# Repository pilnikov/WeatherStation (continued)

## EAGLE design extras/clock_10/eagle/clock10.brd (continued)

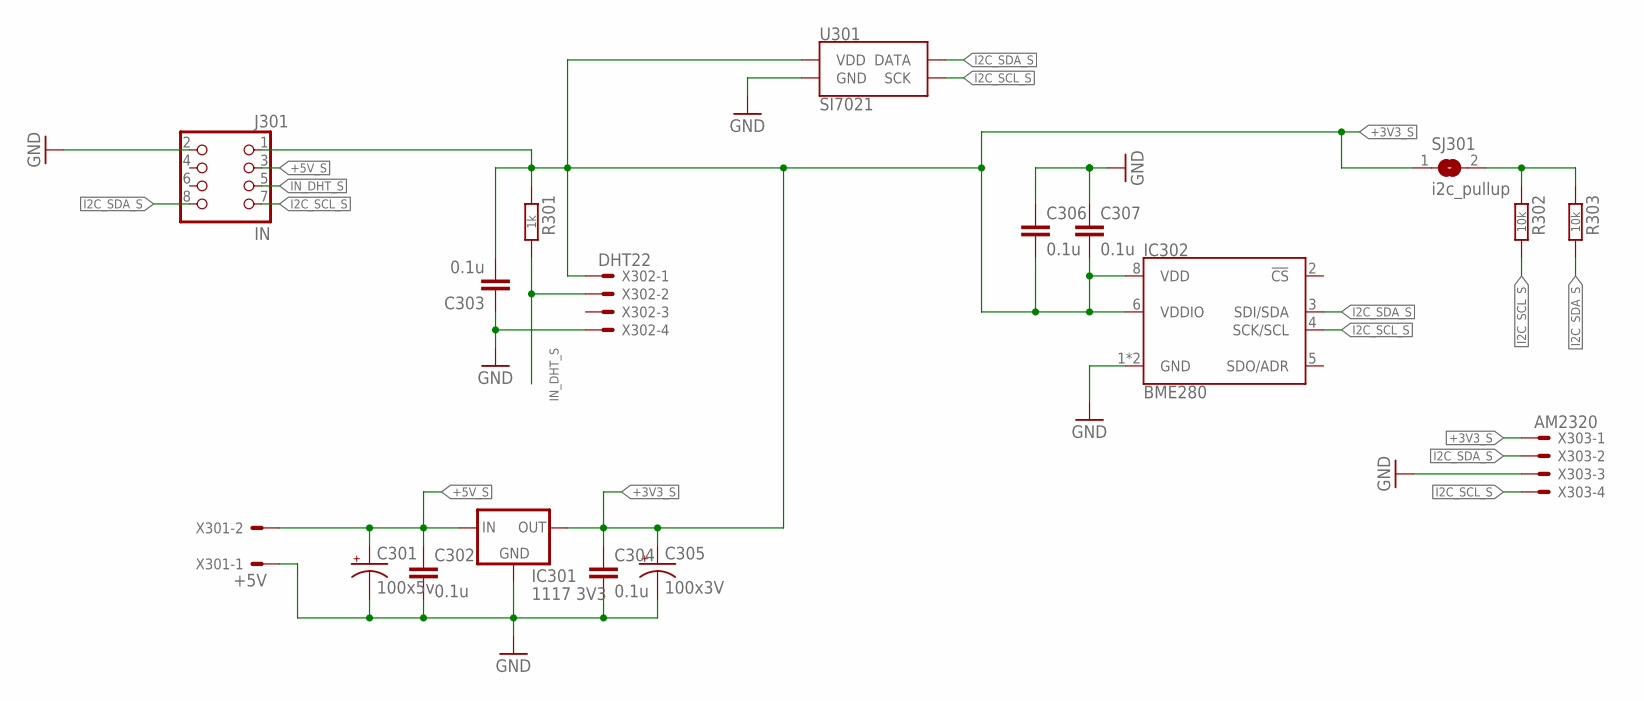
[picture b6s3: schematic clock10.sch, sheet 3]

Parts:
C301: 100x5v; CPOL-RADIAL-100UF-25V
C302, C303, C304, C306, C307: 0.1u; 0603-CAP
C305: 100x3V; CPOL-RADIAL-100UF-25V
IC301: 1117 3V3; SOT223
IC302: BME280; LGA-8-2.5X2.5
J301: IN; 2X04
R301: 1k; R0603
R302, R303: 10k; R0603
SJ301: i2c_pullup; MICROBUILDER_SOLDERJUMPER_ARROW_NOPASTE
U301: SI7021; DFN-6-3X3-SI7021
X301: +5V; 70543-02
X302: DHT22; 70543-04
X303: AM2320; 70543-04

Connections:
+3V3_S: C303.2, C304.1, C305.1 (+), C306.2, C307.2, IC301.2 (OUT), IC301.4 (OUT), IC302.6 (VDDIO), IC302.8 (VDD), J301.1, R301.1, SJ301.1, U301.VDD, X302.1, X303.1
+5V_S: C301.1 (+), C302.1, IC301.3 (IN), J301.3, X301.2
GND: C301.2 (-), C302.2, C303.1, C304.2, C305.2 (-), C306.1, C307.1, IC301.1 (GND), IC302.1 (GND), IC302.7 (GND), J301.2, U301.GND, X301.1, X302.4, X303.3; also elsewhere on the board
I2C_SCL_S: IC302.4 (SCK/SCL), J301.7, R302.2, U301.SCK, X303.4
I2C_SDA_S: IC302.3 (SDI/SDA), J301.8, R303.2, U301.DATA, X303.2
IN_DHT_S: J301.5, R301.2, X302.2
unnamed: R302.1, R303.1, SJ301.2

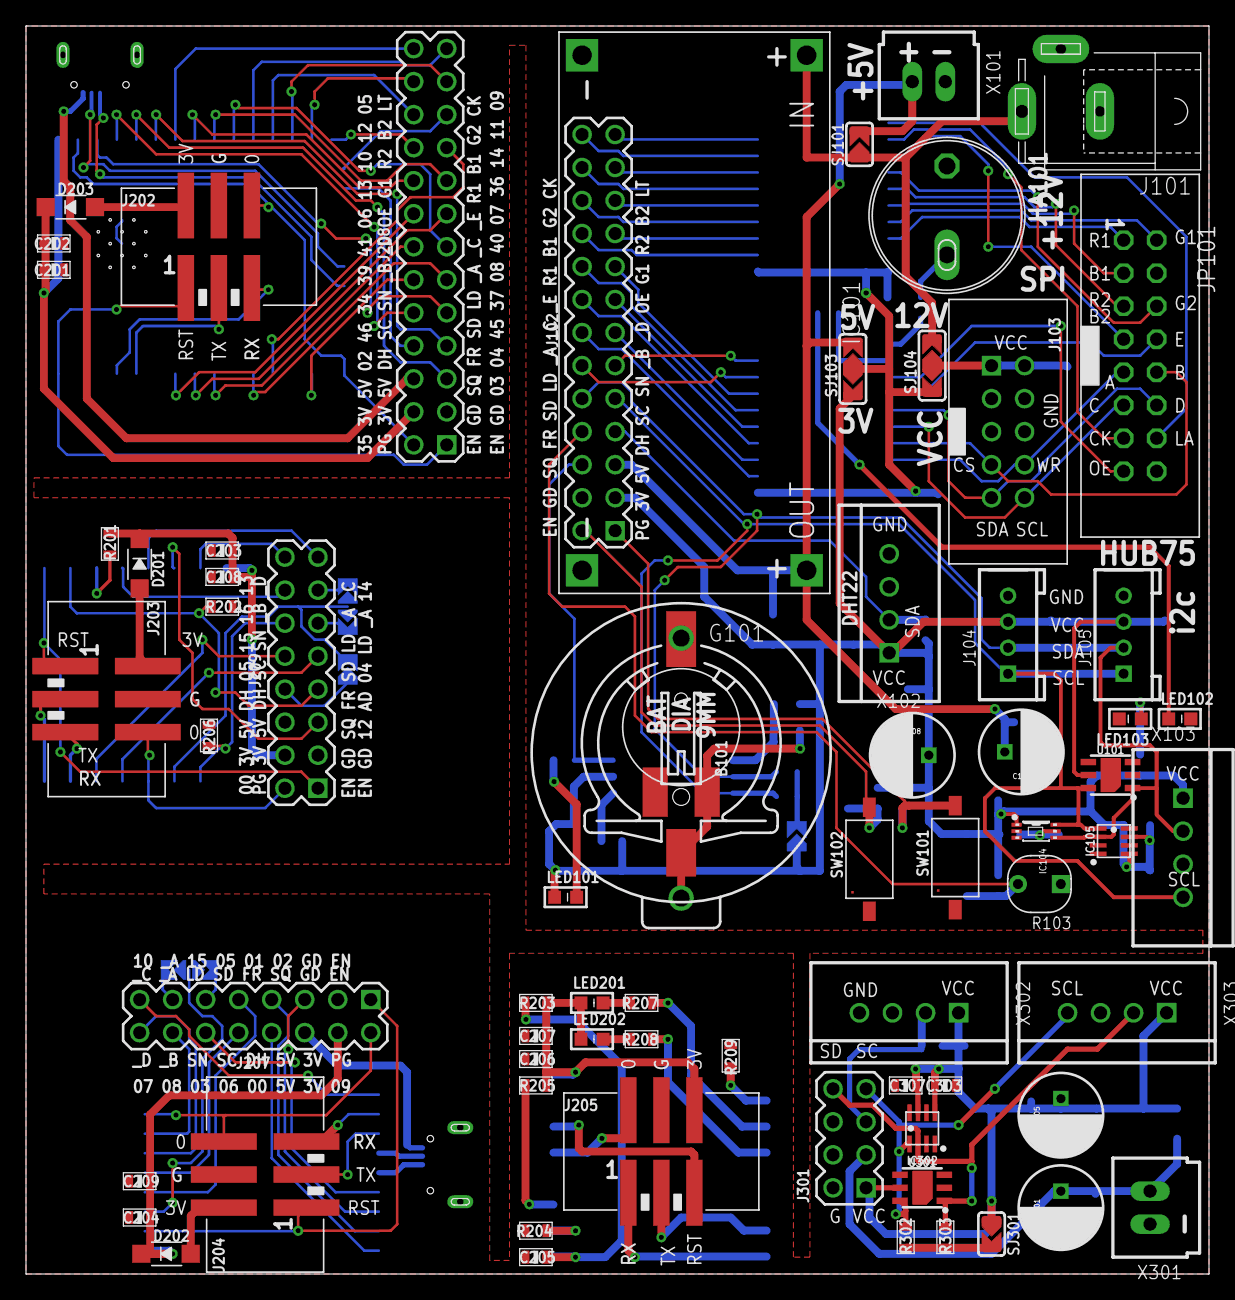
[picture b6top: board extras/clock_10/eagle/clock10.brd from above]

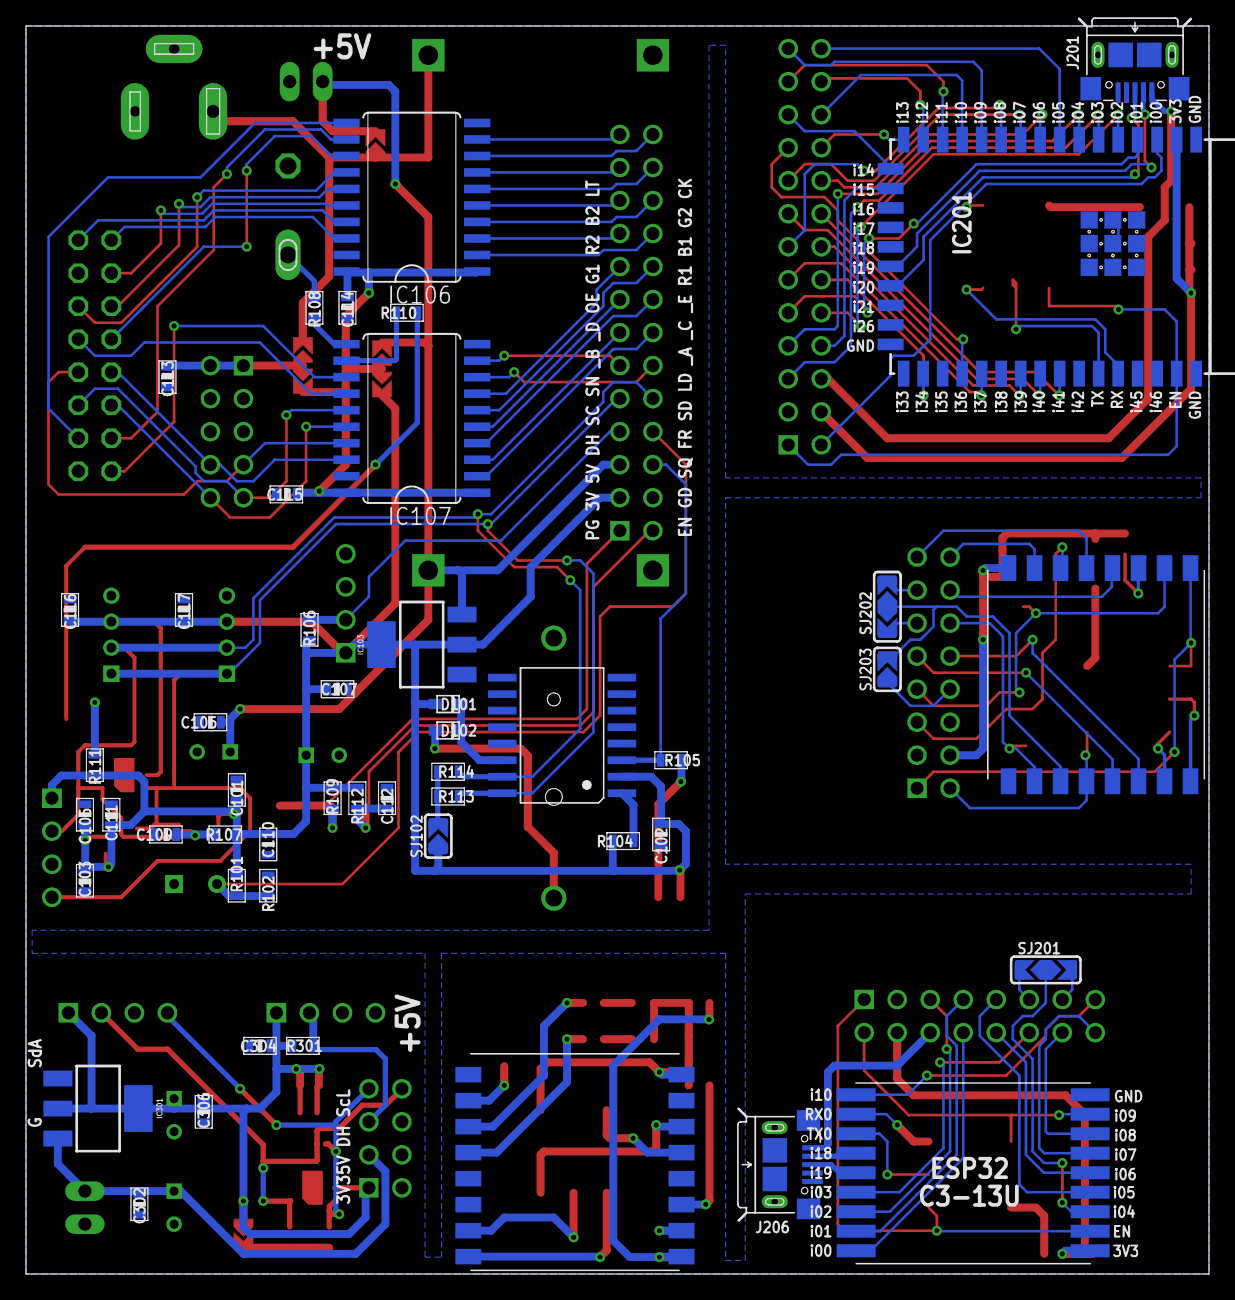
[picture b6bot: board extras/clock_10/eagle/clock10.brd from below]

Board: 2 copper layers, 91.0 x 96.0 mm, 120 parts (49 on the bottom side), 143 nets.

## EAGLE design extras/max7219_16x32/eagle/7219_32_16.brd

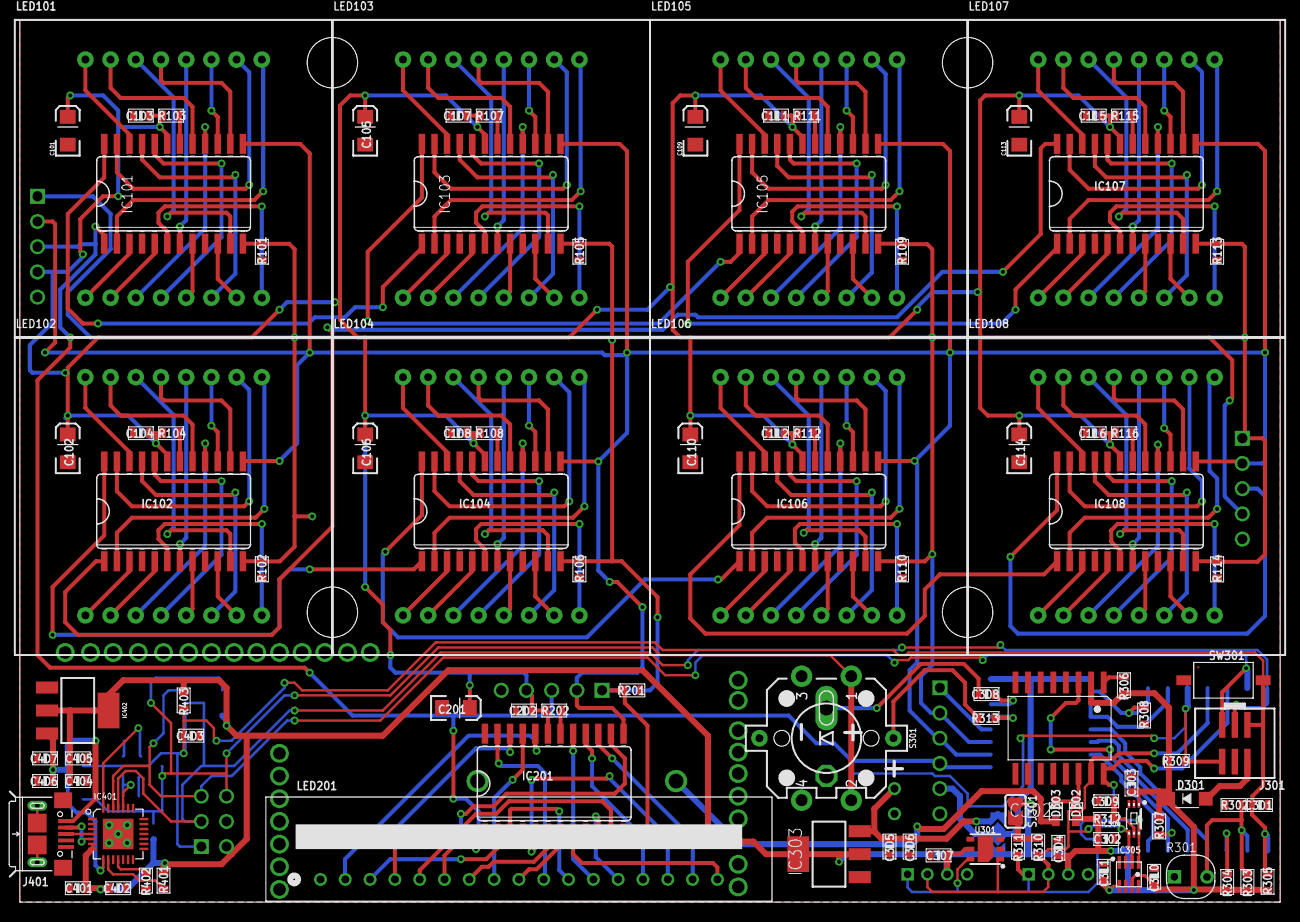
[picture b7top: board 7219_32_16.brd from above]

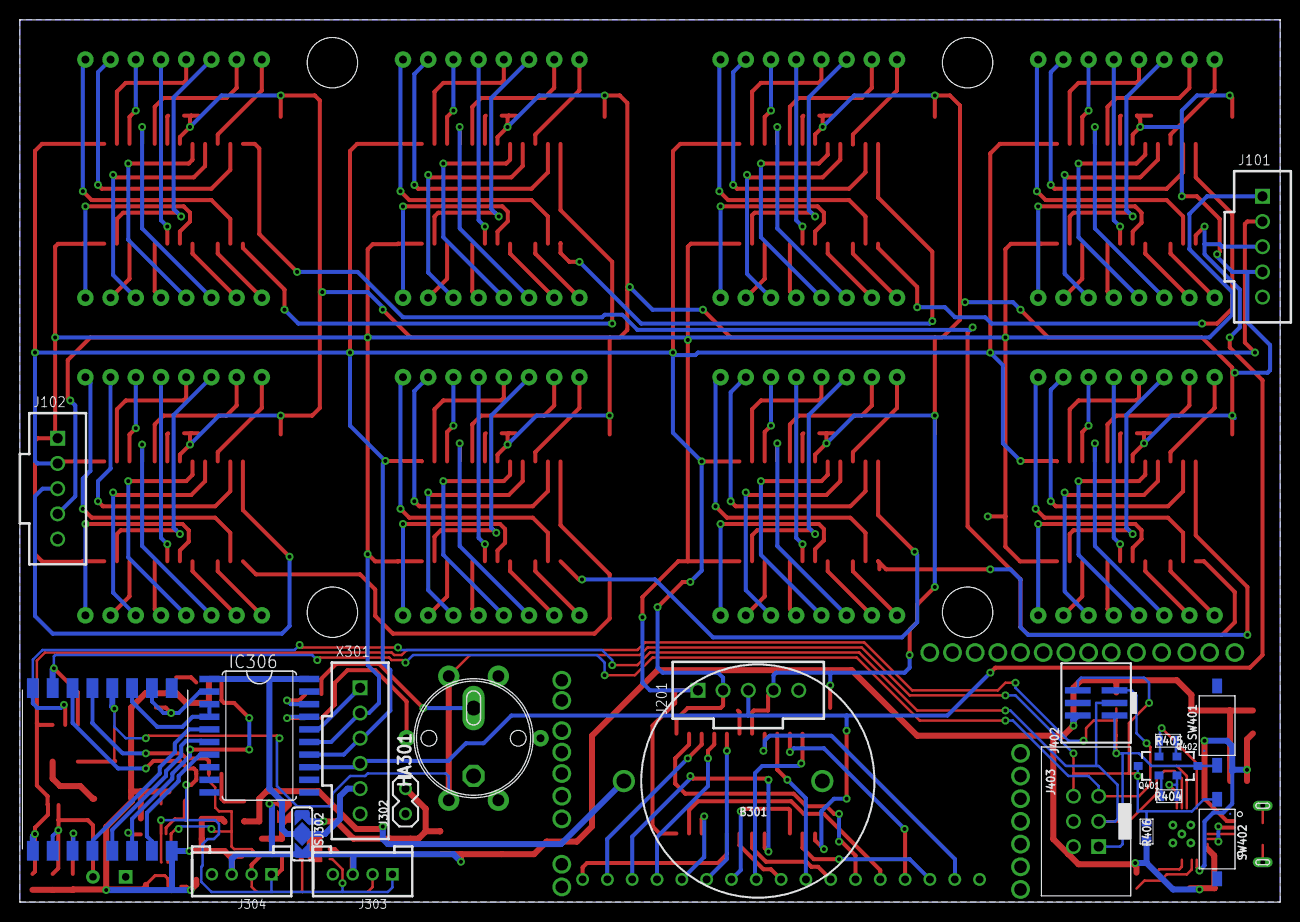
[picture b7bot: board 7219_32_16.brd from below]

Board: 2 copper layers, 127.0 x 88.9 mm, 124 parts (21 on the bottom side), 203 nets.

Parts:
B301: CR2032
C101, C102, C105, C106, C109, C110, C113, C114, C201: 10u; EIA3216
C103, C104, C107, C108, C111, C112, C115, C116, C202, C303, C304, C306, C307, C310, C311, C401, C405, C407: 0.1u; 0603-CAP
C301, C309, C402, C403: 1u; 0603-CAP
C302, C305, C404, C406: 22u; 0603-CAP
C308: 10u; 0603-CAP
D301: IN5819; SOD123
D302, D303: 1N4148; SOD-323F
HA301: BUZZER; PBUZ_12X7.5
IC101, IC102, IC103, IC104, IC105, IC106, IC107, IC108, IC201: MAX7219; SO24L
IC301: ESP12F; ESP12-SMD
IC302: DS3231W; SO16W
IC303: LD1117; SOT223
IC304: BH1750; WSOF6L
IC305: BME280; LGA-8-2.5X2.5
IC306: 74AC245DW; SO20W
IC401: CP2102; QFN28G_0.5-5X5MM
IC402: LM1117_3V3; SOT223
J101, J201: IN; 70543-05
J102: OUT; 70543-05
J301: COM; 2X03_1.27MM_SMT
J302: Vin; 1X02
J303, J304: 4P-2.0; HW4-2.0
J401: usb; USB-B-MICRO-SMD_MY
J402: COM1; 2X03_1.27MM_SMT
J403: COM2; 2X03
LED101, LED102, LED103, LED104, LED105, LED106, LED107, LED108: 1088AS; SEGMENT_BL-M12A881UR
LED201: ALS318A; АЛС318А
Q401, Q402: 7002; SOT23-3
R101, R102, R105, R106, R109, R110, R113, R114, R201, R304, R305, R308, R309, R310, R311, R403, R406: 10k; R0603
R103, R104, R107, R108, R111, R112, R115, R116, R202: 27k; R0603
R301: 10K; SNR2-3.0
R302: 100k; R0603
R303: 220k; R0603
R306, R307, R401, R402: 4.7k; R0603
R312: 1k; R0603
R313, R404, R405: 2k; R0603
S301: SW1; TACTILE_SWITCH_LED_PTH_12MM_KIT
SJ301: i2c_pullup; MICROBUILDER_SOLDERJUMPER_ARROW_NOPASTE
SJ302: MICROBUILDER_SOLDERJUMPER_ARROW_NOPASTE_3
SW301, SW401: RST; MICROPUSH-BUT_TOP
SW402: PRG; MICROPUSH-BUT_TOP
U301: SI7021; DFN-6-3X3-SI7021
X301: DSP; 70543-06

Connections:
1A: IC101.14, LED101.13
1B: IC101.16, LED101.3
1C: IC101.20, LED101.4
1D: IC101.23, LED101.10
1D0: IC101.2, LED101.9
1D1: IC101.11, LED101.14
1D2: IC101.6, LED101.8
1D3: IC101.7, LED101.12
1D4: IC101.3, LED101.1
1D5: IC101.10, LED101.7
1D6: IC101.5, LED101.2
1D7: IC101.8, LED101.5
1DP: IC101.22, LED101.16
1E: IC101.21, LED101.6
1F: IC101.15, LED101.11
1G: IC101.17, LED101.15
2A: IC103.14, LED103.13
2B: IC103.16, LED103.3
2C: IC103.20, LED103.4
2D: IC103.23, LED103.10
2D0: IC103.2, LED103.9
2D1: IC103.11, LED103.14
2D2: IC103.6, LED103.8
2D3: IC103.7, LED103.12
2D4: IC103.3, LED103.1
2D5: IC103.10, LED103.7
2D6: IC103.5, LED103.2
2D7: IC103.8, LED103.5
2DP: IC103.22, LED103.16
2E: IC103.21, LED103.6
2F: IC103.15, LED103.11
2G: IC103.17, LED103.15
3A: IC105.14, LED105.13
3B: IC105.16, LED105.3
3C: IC105.20, LED105.4
3D: IC105.23, LED105.10
3D0: IC105.2, LED105.9
3D1: IC105.11, LED105.14
3D2: IC105.6, LED105.8
3D3: IC105.7, LED105.12
3D4: IC105.3, LED105.1
3D5: IC105.10, LED105.7
3D6: IC105.5, LED105.2
3D7: IC105.8, LED105.5
3DP: IC105.22, LED105.16
3E: IC105.21, LED105.6
3F: IC105.15, LED105.11
3G: IC105.17, LED105.15
4A: IC107.14, LED107.13
4B: IC107.16, LED107.3
4C: IC107.20, LED107.4
4D: IC107.23, LED107.10
4D0: IC107.2, LED107.9
4D1: IC107.11, LED107.14
4D2: IC107.6, LED107.8
4D3: IC107.7, LED107.12
4D4: IC107.3, LED107.1
4D5: IC107.10, LED107.7
4D6: IC107.5, LED107.2
4D7: IC107.8, LED107.5
4DP: IC107.22, LED107.16
4E: IC107.21, LED107.6
4F: IC107.15, LED107.11
4G: IC107.17, LED107.15
5A: IC102.14, LED102.13
5B: IC102.16, LED102.3
5C: IC102.20, LED102.4
5D: IC102.23, LED102.10
5D0: IC102.2, LED102.9
5D1: IC102.11, LED102.14
5D2: IC102.6, LED102.8
5D3: IC102.7, LED102.12
5D4: IC102.3, LED102.1
5D5: IC102.10, LED102.7
5D6: IC102.5, LED102.2
5D7: IC102.8, LED102.5
5DP: IC102.22, LED102.16
5E: IC102.21, LED102.6
5F: IC102.15, LED102.11
5G: IC102.17, LED102.15
6A: IC104.14, LED104.13
6B: IC104.16, LED104.3
6C: IC104.20, LED104.4
6D: IC104.23, LED104.10
6D0: IC104.2, LED104.9
6D1: IC104.11, LED104.14
6D2: IC104.6, LED104.8
6D3: IC104.7, LED104.12
6D4: IC104.3, LED104.1
6D5: IC104.10, LED104.7
6D6: IC104.5, LED104.2
6D7: IC104.8, LED104.5
6DP: IC104.22, LED104.16
6E: IC104.21, LED104.6
6F: IC104.15, LED104.11
6G: IC104.17, LED104.15
7A: IC106.14, LED106.13
7B: IC106.16, LED106.3
7C: IC106.20, LED106.4
7D: IC106.23, LED106.10
7D0: IC106.2, LED106.9
7D1: IC106.11, LED106.14
7D2: IC106.6, LED106.8
7D3: IC106.7, LED106.12
7D4: IC106.3, LED106.1
7D5: IC106.10, LED106.7
7D6: IC106.5, LED106.2
7D7: IC106.8, LED106.5
7DP: IC106.22, LED106.16
7E: IC106.21, LED106.6
7F: IC106.15, LED106.11
7G: IC106.17, LED106.15
8A: IC108.14, LED108.13
8B: IC108.16, LED108.3
8C: IC108.20, LED108.4
8D: IC108.23, LED108.10
8D0: IC108.2, LED108.9
8D1: IC108.11, LED108.14
8D2: IC108.6, LED108.8
8D3: IC108.7, LED108.12
8D4: IC108.3, LED108.1
8D5: IC108.10, LED108.7
8D6: IC108.5, LED108.2
8D7: IC108.8, LED108.5
8DP: IC108.22, LED108.16
8E: IC108.21, LED108.6
8F: IC108.15, LED108.11
8G: IC108.17, LED108.15
9A: IC201.14, LED201.6
9B: IC201.16, LED201.14
9C: IC201.20, LED201.2
9D: IC201.23, LED201.10
9D0: IC201.2, LED201.3
9D1: IC201.11, LED201.5
9D2: IC201.6, LED201.7
9D3: IC201.7, LED201.9
9D4: IC201.3, LED201.11
9D5: IC201.10, LED201.13
9D6: IC201.5, LED201.15
9D7: IC201.8, LED201.17
9DP: IC201.22, LED201.4
9E: IC201.21, LED201.8
9F: IC201.15, LED201.16
9G: IC201.17, LED201.12
+3V3: C302.1, C303.1, C304.2, C307.2, C310.2, C311.2, C401.2, C402.2, C404.1, C405.1, D301.C, D302.A, IC301.VCC, IC302.2, IC303.2, IC303.4, IC304.1, IC305.6, IC305.8, IC401.6, IC401.7, IC402.2, IC402.4, J303.3, J304.3, J402.2, J403.2, R303.2, R304.2, R305.1, R306.2, R307.2, R309.2, R312.1, R401.2, R403.1, R406.2, SJ301.1, SJ302.2, U301.VDD
+5V: C101.A, C102.A, C103.1, C104.1, C105.A, C106.A, C107.1, C108.1, C109.A, C110.A, C111.1, C112.1, C113.A, C114.A, C115.1, C116.1, C201.A, C202.1, IC101.19, IC102.19, IC103.19, IC104.19, IC105.19, IC106.19, IC107.19, IC108.19, IC201.19, J101.4, J102.4, J201.4, R103.1, R104.1, R107.1, R108.1, R111.1, R112.1, R115.1, R116.1, R202.1
ADC: IC301.ADC, R301.2, R302.2, R303.1
BUZ: C308.1, IC306.18
CLK: IC101.13, IC102.13, IC103.13, IC104.13, IC105.13, IC106.13, IC107.13, IC108.13, IC201.13, IC306.14, J101.2, J102.2, J201.2, X301.3
DIN: IC101.1, IC201.1, IC306.13, J101.3, J201.3, X301.4
DOUT1: IC101.24, IC103.1
DOUT2: IC103.24, IC105.1
DOUT3: IC105.24, IC107.1
DOUT4: IC102.1, IC107.24
DOUT5: IC102.24, IC104.1
DOUT6: IC104.24, IC106.1
DOUT7: IC106.24, IC108.1
DOUT8: IC108.24, J102.3
DTR: IC401.28, Q401.2, R405.1
EN: C301.2, C403.2, IC301.RESET, J301.1, J402.1, J403.1, Q402.3, R305.2, R403.2, SW301.B, SW401.A
GND: B301.-, C101.C, C102.C, C103.2, C104.2, C105.C, C106.C, C107.2, C108.2, C109.C, C110.C, C111.2, C112.2, C113.C, C114.C, C115.2, C116.2, C201.C, C202.2, C301.1, C302.2, C303.2, C304.1, C305.2, C306.2, C307.1, C309.2, C310.1, C311.1, C401.1, C402.1, C403.1, C404.2, C405.2, C406.2, C407.2, HA301.C, IC101.4, IC101.9, IC102.4, IC102.9, IC103.4, IC103.9, IC104.4, IC104.9, IC105.4, IC105.9, IC106.4, IC106.9, IC107.4, IC107.9, IC108.4, IC108.9, IC201.4, IC201.9, IC301.GND, IC302.5, IC302.6, IC302.7, IC302.8, IC302.9, IC302.10, IC302.11, IC302.12, IC302.13, IC303.1, IC304.2, IC304.3, IC305.1, IC305.7, IC306.10, IC306.19, IC401.3, IC401.29, IC401.HG1, IC401.HG2, IC401.HG3, IC401.HG4, IC401.HG5, IC402.1, J101.5, J102.5, J201.5, J301.4, J302.1, J303.4, J304.4, J401.GND, J401.SH@1, J401.SH@2, J401.SH@3, J401.SH@4, J401.SH@5, J401.SH@6, J402.4, J403.4, R101.1, R102.1, R105.1, R106.1, R109.1, R110.1, R113.1, R114.1, R201.1, R301.1, R302.1, R308.1, R402.2, S301.3, S301.4, S301.C, SW301.A, SW301.SH0, SW401.B, SW401.SH0, SW402.B, SW402.SH0, U301.GND, X301.6
GPIO0: IC301.GPIO0, J301.6, J402.6, J403.6, Q401.3, R309.1, R406.1, S301.1, S301.2, SW402.A
GPIO2: IC301.GPIO2, IC306.3, IC306.4
GPIO12: IC301.GPIO12, IC302.3, R307.1
GPIO13: IC301.GPIO13, IC306.7
GPIO14: IC301.GPIO14, IC306.6
GPIO15: IC301.GPIO15, IC306.2, R308.2
GPIO16: IC301.GPIO16, IC306.5
ISET1: IC101.18, R103.2
ISET2: IC103.18, R107.2
ISET3: IC105.18, R111.2
ISET4: IC107.18, R115.2
ISET5: IC102.18, R104.2
ISET6: IC104.18, R108.2
ISET7: IC106.18, R112.2
ISET8: IC108.18, R116.2
ISET9: IC201.18, R202.2
LED: IC306.17, R313.1
LOAD: IC101.12, IC102.12, IC103.12, IC104.12, IC105.12, IC106.12, IC107.12, IC108.12, IC201.12, IC306.15, J101.1, J102.1, J201.1, R101.2, R102.2, R105.2, R106.2, R109.2, R110.2, R113.2, R114.2, R201.2, X301.2
unnamed: D302.C, D303.C, IC302.14
unnamed: R313.2, S301.A
unnamed: IC401.4, J401.D+
unnamed: IC401.5, J401.D-
unnamed: IC301.CH_PD, R304.1
unnamed: Q401.1, R404.2
unnamed: C308.2, HA301.A
unnamed: Q402.1, R405.2
unnamed: C309.1, IC304.5, R312.2
unnamed: IC302.1, R306.1
unnamed: IC401.11, R402.1
unnamed: IC401.9, R401.1
unnamed: R310.1, R311.1, SJ301.2
unnamed: D301.A, J301.2
unnamed: B301.+, D303.A
RTS: IC401.24, Q402.2, R404.1
RX: IC301.RXD0, IC401.26, J301.5, J402.5, J403.5
SCL: IC301.GPIO5, IC302.16, IC304.6, IC305.4, J303.1, J304.1, R311.2, U301.SCK
SDA: IC301.GPIO4, IC302.15, IC304.4, IC305.3, J303.2, J304.2, R310.2, U301.DATA
TX: IC301.TXD0, IC401.25, J301.3, J402.3, J403.3
VBUS: C406.1, C407.1, IC401.8, IC402.3, J401.VBUS
VIN: C305.1, C306.1, IC303.3, J302.2, SJ302.3
V_OUT: IC306.1, IC306.20, SJ302.1, X301.5
WR: IC306.16, X301.1

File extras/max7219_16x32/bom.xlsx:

74AC245DW | 74AC245DW | IC306
BH1750 | BH1750 | IC304
BME280 | BME280 | IC305
0.1u | CAP0603-CAP | C103, C104, C107, C108, C111, C112, C115, C116, C202, C303, C304, C306, C307, C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
10u | CAP0603-CAP | C308
1u | CAP0603-CAP | C301, C309, C402, C403
22u | CAP0603-CAP | C302, C305, C404, C406
10u | CAP_POL1206 | C101, C102, C105, C106, C109, C110, C113, C114, C201
IN5819 | DIODE-SOD123 | D301
1N4148 | DIODESOD-323F | D302, D303
DS3231W | DS3231W | IC302
MAX7219 | MAX7219CNGSO24 | IC101, IC102, IC103, IC104, IC105, IC106, IC107, IC108, IC201
2N7002 | MOSFET-NCH-2N7002 | Q401, Q402
100k | R-EU_R0603 | R302
10k | R-EU_R0603 | R101, R102, R105, R106, R109, R110, R113, R114, R201, R304, R305, R308, R309, R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
1k | R-EU_R0603 | R312
220k | R-EU_R0603 | R303
27k | R-EU_R0603 | R103, R104, R107, R108, R111, R112, R115, R116, R202
2k | R-EU_R0603 | R313, R404, R405
4.7k | R-EU_R0603 | R306, R307, R401, R402
SI7021 | SI7021 | U301
usb | USB_MICRO-BFEMALE_SMT_ | J401
LD1117 | V_REG_LD1117VXXSMD | IC303, IC402

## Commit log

2018-07-16 First Add
2018-07-16 Replace old
2018-07-16 Add OWM
2018-07-16 Add instructions
2018-07-16 Little bug fix
2018-07-16 New version
2018-07-16 IP to str change
2018-07-17 Modify display functions
2018-07-18 Move some methods from fsys to fdsp
2018-07-20 Modify messages output methods
2018-07-24 Replace StaticJsonBuffer to Dynamic
2018-07-26 7 seg modify
2018-07-31 Msg functions modify
2018-08-01 Unsupported
2018-08-01 Msg move here
2018-08-01 Move msg to fdsp library
2018-08-01 Some bug fix
2018-08-01 New display methods
2018-08-07 New other version
2018-08-07 Change tm1637 lib
2018-08-08 Modify sound
2018-08-10 first try add big matrix display
2018-08-13 Add matrix 32x64 for esp32
2018-08-14 Add draw part char
2018-08-14 Adopt for esp32 (compartible with tone())
2018-08-14 Moved to esp32 step2
2018-08-15 Add matrix 32x64
2018-08-16 Add ili9341(beta)
2018-08-19 Esp32 forwarded
2018-09-21 Bug Fix
2018-09-27 Add tablo on mega2560
2019-07-31 Serial update (json e.t.s.)
2019-07-31 add new bin
2019-07-31 Bin update
2020-01-16 upd lib
2020-01-16 upd snr
2020-01-16 Delete config.json
    non correct
2020-01-16 add correct config
2020-01-16 upd_work 17_01_20
2020-01-17 upd json
2020-01-17 add thermostate
2020-01-17 fix little bug
2020-01-17 little bug fix
2020-01-20 fix tablo
2020-08-04 update libraries
2020-12-27 modify snr
2020-12-27 debug for 8266
2020-12-27 debug analog input
2020-12-27 next step for mod sens
2020-12-27 little fix bug
2020-12-28 next step
2021-02-16 new displays base
2021-02-16 recover running string (temporary)
2021-02-17 add new shifter
2021-02-18 replace max7219 render mechanism
2021-02-18 bad scrolling, temporary ver
2021-02-19 working commit
2021-02-20 modify msg
2021-02-23 all work instead 7 seg
2021-02-24 repair 7seg
2021-02-25 ht1633 add
2021-02-25 broken scrolling return ht33 14s x8
2021-02-26 scroll returned
2021-02-28 return sure 1632
2021-03-02 ht bug fix
2021-03-02 14 bug fix
2021-03-02 add modify lib
2021-03-03 little fixing
2021-03-03 custom 2 work now
2021-03-09 litlle fix
2021-03-10 snd no delay
2021-03-11 snd no delay first step
2021-03-17 new board
2021-03-17 add snd&led out inversion
2021-03-22 snr lib modify
2021-03-25 fix prototypes
2021-03-25 change struct
2021-04-02 tablo modify beta
2021-04-05 m3216 return first step
2021-05-24 mega prepare
2021-05-27 add meteo_gps
2021-05-30 Big optimization for mega2560
2021-05-30 remove vs
2021-05-30 remove release
2021-05-31 snd optimization
2021-06-06 sound repare
2021-06-07 littlefs
2021-06-07 gpio + snd stable
2021-06-07 config mod
2021-06-10 tablo mod stable
2021-06-11 snd mod
2021-06-15 esp32 adopt
2021-06-16 lib correct
2021-06-16 json upg
2021-06-20 memory optim
2021-06-23 warn supress
2021-06-27 add some
2021-06-28 clearing
2021-06-28 opti
2021-06-29 dsp opti
2021-06-29 dsp opti2
2021-06-29 disp opti3
2021-06-29 func opti
2021-06-29 esp32 upd
2021-06-29 esp32 upd2
2021-06-30 irq mod
2021-06-30 rtc new
2021-07-01 little opti
2021-07-01 stable
2021-07-02 si lib
2021-07-04 memory opt
2021-07-04 m3216 return
2021-07-07 little msg opt
2021-07-07 msg correct
2021-07-07 correct msg 2
2021-07-09 tablo -> ws_rt
2021-07-11 adopt for esp32 (beta)
2021-07-16 snd for esp32 return
2021-07-16 esp32 optimized
2021-07-18 irq for esp32
2021-07-22 beta
2021-07-22 beta2
2021-07-24 semi stab
2021-07-24 http update for esp32 return
2021-07-27 beta3
2021-07-27 replace type of st1 from string to char*
2021-07-27 add adafruit protomatter
2021-07-27 matrix2
2021-07-28 protomatter 2
2021-08-02 lcd back
2021-08-05 -time lib
2021-08-06 rtc for tablo
2021-08-09 keyb+alarm
2021-08-10 rtc to work
2021-08-12 rtc work property
2021-08-20 ad marquee
2021-08-25 failsafe for config
2021-08-26 add news (part1)
2021-08-27 adopt for new red board
2021-08-29 repair matrix
2021-08-30 add news step 2
2021-08-30 add news part 3 (todo add json answer)
2021-08-31 news part 4
2021-08-31 news part 5
2021-08-31 bz2 -
2021-09-08 add max 16x32 mono
2021-09-09 snr rework
2021-09-09 conf adopt for esp32
2021-09-09 max 7219 16x32 work
2021-09-10 little bug
2021-10-01 add c3
2021-10-06 optimize web
2021-10-07 optimize server
2021-10-15 add display test
2021-10-18 lib upd
2021-10-19 add board max7219
2021-10-19 add esp32 board
2021-10-28 с3 upd
2021-11-01 add disp opt
2021-11-02 add disp options time u/d + color
2021-11-06 add esm and server mod
2021-11-06 patch not good
2021-11-08 firq rename
2021-11-12 add new board
2021-11-14 add s2
2021-11-17 fix spi init
2021-11-18 wifi upg
2021-11-19 wifi 2
2021-11-22 ssdp fix
2021-12-09 ota repair
2022-01-10 add 18b20
2022-01-10 add one wire
2022-01-10 ad ds18b20 2
2022-01-14 add new boards
2022-01-15 upg board
2022-01-21 add relay
2022-01-25 web mod
2022-01-26 web gooding
2022-01-31 add test wifi + new boards
2022-02-01 add wifi.lib
2022-02-01 add wifi_cur
2022-02-03 add rtc lib
2022-02-03 upd lbr
2022-02-05 add rtc
2022-02-06 bug fix2
2022-02-10 lib opti
2022-02-10 add m7219 test
2022-02-13 mod snr
2022-02-14 upd snr2
2022-02-14 upd snr 3
2022-02-14 mod snr 3
2022-02-14 bug in snr
2022-02-15 add json request
2022-02-16 add style.css & script.js
2022-02-17 start migrate to json
2022-02-17 migrate to json get req step2
2022-02-18 new wifi lib
2022-02-18 migrate to json rec / first fix result
2022-02-18 test rtc mod step1
2022-02-19 migrate to json fix step3
2022-02-19 wifi corr
2022-02-19 time corr
2022-02-21 set time not working prop
2022-02-21 wifi.cor
2022-02-21 time mod + stop serv ban
2022-02-22 rtc big mod step1
2022-02-23 rtc lib is ready
2022-02-27 split rtc msg
2022-03-02 stru upd
2022-03-02 mod stru 2
2022-03-03 structure mod 3
2022-03-03 structure mod 4 stable
2022-03-03 upd bin
2022-03-03 mod stru 5 unstable
2022-03-03 bug fix part
2022-03-04 replace htu
2022-03-05 upd scroll
2022-03-05 mod stru 5 stable
2022-03-07 upd display
2022-03-07 test disp upd
2022-03-10 mod stru 6
2022-05-27 forecast correct
2022-08-26 lcd scroll repair
2023-01-29 add touch button test
2023-01-30 mod touch test step2 (add balance ad push to server)
2023-01-30 touch test step 3 add receiver
2023-01-31 mod for relay, mod def conf mech
2023-01-31 packing config to class
2023-01-31 little fix for avr
2023-02-03 update for new makuna (need add work)
2023-02-03 mod for new makuna stage 2(stable)
2023-02-07 fine text
2023-02-10 relay mod step 1
2023-02-12 Add files via upload
    mod relay
2023-02-12 1111
2023-02-13 relay mod (stage 3)
2023-02-13 relay mod (stable)
2023-02-19 upd stru
2023-02-19 del unused files
2024-11-04 code corrected
2024-11-04 Add files via upload
    code modifed
2025-02-25 new release dsp mod gpio mod
2025-02-25 display mod (not end)
2025-02-25 add new (modifed) lib for display
2025-02-26 disp mod stage 2 (semi work)
2025-02-27 disp mod part next not working!!!
2025-02-27 display mod next step - semi work
2025-02-27 add old lib for recover
2025-02-28 display mod next step working
2025-03-04 display mod next step matrix work segment - not
2025-03-17 ht1632 repair news repair
2025-03-30 upd web names handlers + ht1632 working ok!
2025-04-10 m1632 colorized now!
2025-04-10 disp brightness range tune
